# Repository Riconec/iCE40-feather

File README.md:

# iCE40-feather

## An iCE40UP5K FPGA in a Feather compatible form factor

* iCE40UP5k FPGA in a QFN-48 package
    * 5280 Logic Cells
* 20 IO broken out to Feather, 4 additional IO on bottom of board
* FT2232 provides programming and UART interface over a Micro USB connector
* 32 MBit SPI Flash
* Onboard RGB LED, user LED, TX/RX LEDs

### Additional FeatherWings  
* 6x6 LED Matrix + 4 Buttons + RGB LED
* DIP Switch + 7 Segment Display
* Feather to Dual PMOD breakout 

### Software
* Compatible with the open source [IceStorm](http://www.clifford.at/icestorm/#install) toolchain
* Thanks to [Piotr Esden-Tempski](https://twitter.com/esden) and his [iCEBreaker examples](https://github.com/icebreaker-fpga/icebreaker-examples) as a starting point for the firmware development.

### Additional Images

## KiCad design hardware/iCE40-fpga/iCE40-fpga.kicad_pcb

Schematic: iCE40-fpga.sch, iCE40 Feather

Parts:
C1, C2, C4, C10, C18: 10u; C_0603_1608Metric
C3, C7, C8, C11, C16, C19, C21, C22, C24: 100n; C_0603_1608Metric
C5, C6: 1u; C_0603_1608Metric
D1: ORG; LED_0603_1608Metric
D2: MBR120; D_SOD-123F
D3, D8: GRN; LED_0603_1608Metric
D4: CDBU0520; D_SOD-523
D5: BLU; LED_0603_1608Metric
D6: LED_RGBA; LED_0606
D7: RED; LED_0603_1608Metric
F1: 500mA; Fuse_0805_2012Metric
FB1: 600R; Ferrite_Bead_0603
J1: USB_B_Micro; USB_Micro_Aliexpress
J2: JST_PH; JST_PH_S2B-PH-SM4-TB_1x02-1MP_P2.00mm_Horizontal
J3: Feather; featherwing
Q1: DMP2045U; SOT-23
R1, R4: 100K; R_0603_1608Metric
R3, R5: 10K; R_0603_1608Metric
R6: 100R; R_0603_1608Metric
RN1: 10K; R_Array_Convex_4x0402
RN3: 330R; R_Array_Convex_4x0402
RN4, RN5: 2K2; R_Array_Convex_4x0402
TP1: IO_22; TestPoint_Pad_D1.5mm
TP2: IO_20; TestPoint_Pad_D1.5mm
TP3: IO_23; TestPoint_Pad_D1.5mm
TP4: IO_21; TestPoint_Pad_D1.5mm
U1: MCP73831-2-OT; SOT-23-5
U2: W25Q32JVZP; WSON-8-1EP_6x5mm_P1.27mm_EP3.4x4.3mm
U3: AP2112K-3.3; SOT-23-5
U4: ICE40UP5K-SG48ITR; QFN-48-1EP_7x7mm_P0.5mm_EP5.6x5.6mm_ThermalVias
U5: NCV8114ASN120T1G; TSOT-23-5
X1: DSC6101CI1A; CDFN_3.2x2.5mm_XO; MPN DSC6101CI1A-012.0000T

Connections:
+1V2: C6.1, C10.1, C16.1, C18.1, C19.1, C22.1, R6.2, U4.5 (VCC), U4.30 (VCC), U5.5 (OUT)
+5V: D1.2 (A), D2.2 (A), FB1.2, J3.26 (VBUS), Q1.1 (G), R1.1, U1.4 (VDD)
+BATT: C2.1, J2.1, J3.28 (VBAT), Q1.3 (D), U1.3 (VBAT)
/FLASH_MISO|IO1: U2.2 (DO(IO1)), U4.17 (IOB_33b_SPI_SI); also elsewhere on the board
/FLASH_MOSI|IO0: U2.5 (DI(IO0)), U4.14 (IOB_32a_SPI_SO); also elsewhere on the board
/FLASH_SCK: RN1.1 (R1.1), U2.6 (CLK), U4.15 (IOB_34a_SPI_SCK); also elsewhere on the board
/FLASH_SS: RN1.4 (R4.1), U2.1 (~CS), U4.16 (IOB_35b_SPI_SS); also elsewhere on the board
/FLASH_nHOLD|IO3: RN1.3 (R3.1), U2.7 (IO3)
/FLASH_nWP|IO2: RN1.2 (R2.1), U2.3 (IO2)
/ICE_CDONE: D5.2 (A), RN4.2, U4.7 (CDONE); also elsewhere on the board
/ICE_CLK: U4.35 (IOT_46b_G0), X1.3 (OUT); also elsewhere on the board
/IO_0: J3.5 (IO0), U4.25 (IOT_36b)
/IO_1: J3.6 (IO1), U4.26 (IOT_39a)
/IO_2: J3.7 (IO2), U4.27 (IOT_38b)
/IO_3: J3.8 (IO3), U4.28 (IOT_41a)
/IO_4: J3.9 (IO4), U4.36 (IOT_48b)
/IO_5: J3.10 (IO5), U4.31 (IOT_42b)
/IO_6: J3.11 (IO6|SCK), U4.32 (IOT_43a)
/IO_7: J3.12 (IO7|MOSI), U4.37 (IOT_45a_G1)
/IO_8: J3.13 (IO8|MISO), U4.38 (IOT_50b)
/IO_9: J3.14 (IO9|RX), U4.43 (IOT_49a)
/IO_10: J3.15 (IO10|TX), U4.44 (IOB_3b_G6)
/IO_11: J3.17 (IO11|SDA), U4.48 (IOB_4a)
/IO_12: J3.18 (IO12|SCL), U4.2 (IOB_6a)
/IO_13: J3.19 (IO13), U4.3 (IOB_9b)
/IO_14: J3.20 (IO14), U4.4 (IOB_8a)
/IO_15: J3.21 (IO15), U4.6 (IOB_13b)
/IO_16: J3.22 (IO16), U4.9 (IOB_16a)
/IO_17: J3.23 (IO17), U4.10 (IOB_18a)
/IO_18: J3.24 (IO18), U4.11 (IOB_20a)
/IO_19: J3.25 (IO19), U4.12 (IOB_22b)
/LDO_EN: J3.27 (EN), R4.2, U3.3 (EN)
/UART_RX: RN4.6, U4.23 (IOT_37a); also elsewhere on the board
/UART_TX: RN4.5, U4.21 (IOB_23b); also elsewhere on the board
/USB_N: J1.2 (D-); also elsewhere on the board
/USB_P: J1.3 (D+); also elsewhere on the board
/nICE_CRESET: J3.1 (nRST), R5.2, U4.8 (~CRESET); also elsewhere on the board
/nLED: RN5.4, U4.47 (IOB_2a)
/nLED_BLU: RN3.1 (R1.1), U4.39 (RGB0)
/nLED_GRN: RN3.2 (R2.1), U4.40 (RGB1)
/nLED_RED: RN3.4 (R4.1), U4.41 (RGB2)
unnamed: C1.1, C5.1, D2.1 (K), Q1.2 (S), R4.1, U3.1 (VIN), U5.1 (IN), U5.3 (EN)
unnamed: D1.1 (K), RN5.8
unnamed: D4.1 (K), U4.24 (VPP_2V5)
unnamed: D6.1 (RK), RN3.5 (R4.2)
unnamed: D6.2 (GK), RN3.7 (R2.2)
unnamed: D6.3 (BK), RN3.8 (R1.2)
unnamed: D7.1 (K), RN5.5
unnamed: F1.1, FB1.1
unnamed: F1.2, J1.1 (VBUS)
unnamed: R3.1, U1.5 (PROG)
unnamed: R6.1, U4.29 (VCCPLL)
unnamed: RN5.1, U1.1 (STAT)
unnamed: TP1.1, U4.42 (IOT_51a)
unnamed: TP2.1, U4.46 (IOB_0a)
unnamed: TP3.1, U4.45 (IOB_5b)
unnamed: TP4.1, U4.13 (IOB_24a)

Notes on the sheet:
Power Regulation
FPGA Power
RGB LED
SPI Flash
USB / FTDI Programmer / UART
Oscillator
iCE40UP5K FPGA IO
User LED
Feather Footprint
LIPO Charging
LIPO JST Connector
UART LEDs

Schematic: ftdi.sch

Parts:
C26, C30, C31, C32, C33, C34, C35, C36: 100n; C_0603_1608Metric
C28: 4u7; C_0603_1608Metric
FB2, FB3: 600R; BEADC1608X95N
R13: 2K2; R_0603_1608Metric
R14: 10K; R_0603_1608Metric
R15: 12K; R_0603_1608Metric
RN2: 10K; R_Array_Convex_4x0402
U7: 93C46B; SOT-23-6
U8: FT2232H; QFN-64-1EP_9x9mm_P0.5mm_EP4.7x4.7mm_ThermalVias

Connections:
+1V8: C28.1, C30.1, U7.12, U7.37, U7.49, U7.64
/FLASH_MISO|IO1: U7.18; also elsewhere on the board
/FLASH_MOSI|IO0: U7.17; also elsewhere on the board
/FLASH_SCK: U7.16; also elsewhere on the board
/FLASH_SS: U7.21; also elsewhere on the board
/FTDI Programmer / UART/FT_EECLK: RN2.3 (R3.1), U7.62; also elsewhere on the board
/FTDI Programmer / UART/FT_EECS: RN2.2 (R2.1), U7.63; also elsewhere on the board
/FTDI Programmer / UART/FT_EEDATA: R13.1, RN2.4 (R4.1), U7.61; also elsewhere on the board
/ICE_CDONE: U7.23; also elsewhere on the board
/ICE_CLK: U7.2; also elsewhere on the board
/UART_RX: U7.38; also elsewhere on the board
/UART_TX: U7.39; also elsewhere on the board
/USB_N: U7.7; also elsewhere on the board
/USB_P: U7.8; also elsewhere on the board
/nICE_CRESET: U7.24; also elsewhere on the board
unnamed: C31.1, FB2.1, U7.9
unnamed: C32.1, FB3.1, U7.4
unnamed 60: R13.2; also elsewhere on the board
unnamed: R14.1, U7.14
unnamed: R15.1, U7.6

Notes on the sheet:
FTDI Programmer / UART

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
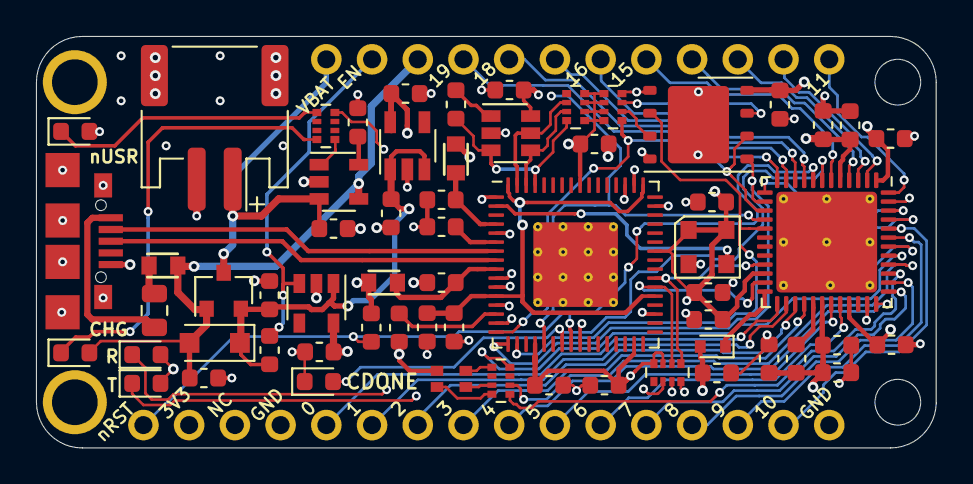
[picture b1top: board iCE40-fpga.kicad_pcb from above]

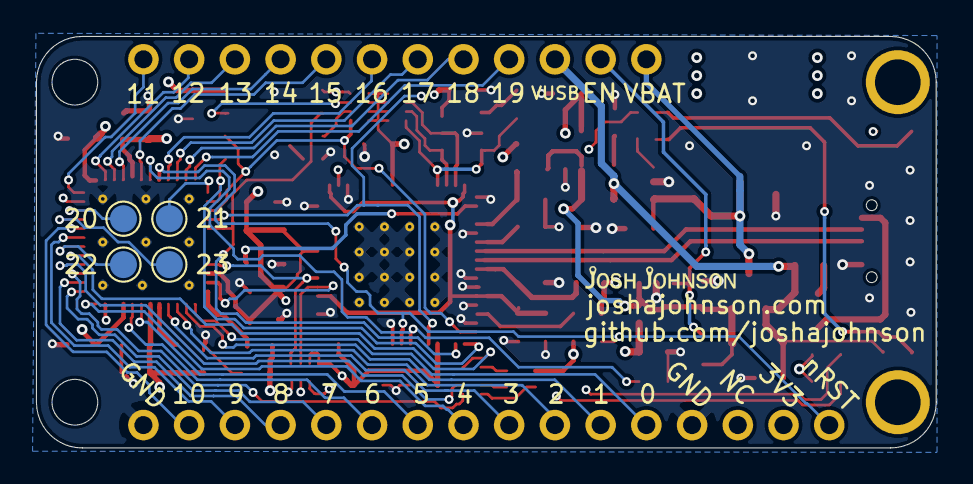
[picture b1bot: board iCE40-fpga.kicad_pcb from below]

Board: 4 copper layers, 50.0 x 22.9 mm, 66 parts (4 on the bottom side), 70 nets.

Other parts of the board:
U6: 93C46B; SOT-23-6

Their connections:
/FTDI Programmer / UART/FT_EECLK: U6.4; also elsewhere on the board
/FTDI Programmer / UART/FT_EECS: U6.5; also elsewhere on the board
/FTDI Programmer / UART/FT_EEDATA: U6.3; also elsewhere on the board
unnamed 60: U6.1; also elsewhere on the board

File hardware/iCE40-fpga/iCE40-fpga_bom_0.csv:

Component,Description,Part,References,Value,Footprint,Quantity Per PCB,Datasheet,MPN
1,Unpolarized capacitor,C,C3 C7 C8 C11 C16 C19 C21 C22 C24 C26 C30 C31 C32 C33 C34 C35 C36,100n,C_0603_1608Metric,17,~,
2,Unpolarized capacitor,C,C1 C2 C4 C10 C18,10u,C_0603_1608Metric,5,~,
3,Unpolarized capacitor,C,C5 C6,1u,C_0603_1608Metric,2,~,
4,Unpolarized capacitor,C,C28,4u7,C_0603_1608Metric,1,~,
5,Light emitting diode,LED,D5,BLU,LED_0603_1608Metric,1,~,
6,Diode,D,D4,CDBU0520,D_SOD-523,1,~,
7,Light emitting diode,LED,D7,LED,LED_0603_1608Metric,1,~,
8,"RGB LED, anode/red/green/blue",LED_RGBA,D6,LTST-C19HE1WT,0606LED,1,~,
9,Schottky diode,D_Schottky,D2,MBR120,D_SOD-123F,1,~,
10,Light emitting diode,LED,D1,ORG,LED_0603_1608Metric,1,~,
11,"Resettable fuse, polymeric positive temperature coefficient",Polyfuse,F1,500mA,Fuse_0805_2012Metric,1,~,
12,Ferrite bead,Ferrite_Bead_PWR,FB1 FB2 FB3,600R ,BEADC1608X95N,3,~,
13,,Feather,J3,Feather,PCB_FeatherWing,1,,
14,"Generic connector, single row, 01x02, script generated (kicad-library-utils/schlib/autogen/connector/)",Conn_01x02_Male,J2,JST_PH,JST_PH_S2B-PH-SM4-TB_1x02-1MP_P2.00mm_Horizontal,1,~,
15,USB Micro Type B connector,USB_B_Micro,J1,USB_B_Micro,MicroUSB_Aliexpress,1,~,
16,"P-MOSFET transistor, gate/source/drain",Q_PMOS_GSD,Q1,DMP2045U,SOT-23,1,~,
17,Resistor,R,R1 R4,100K,R_0603_1608Metric,2,~,
18,Resistor,R,R6,100R,R_0603_1608Metric,1,~,
19,Resistor,R,R3 R5 R14,10K,R_0603_1608Metric,3,~,
20,Resistor,R,R15,12K,R_0603_1608Metric,1,~,
21,Resistor,R,R8,1K,R_0603_1608Metric,1,~,
22,Resistor,R,R2 R7 R13,2K2,R_0603_1608Metric,3,~,
23,"4 resistor network, parallel topology, DIP package",R_Pack04,RN1 RN2,10K,R_Array_Convex_4x0402,2,~,
24,"4 resistor network, parallel topology, DIP package",R_Pack04,RN3,1K,R_Array_Convex_4x0402,1,~,
25,"Serial EEPROM, 93 Series, 5.0V, DIP-8/SOIC-8",93C46B,U7,93C46B,SOT-23-6,1,http://ww1.microchip.com/downloads/en/DeviceDoc/20001749K.pdf,
26,"600mA low dropout linear regulator, with enable pin, 2.5V-6V input voltage range, 1.2V fixed positive output, SOT-23-5 package",AP2112K-1.2,U5,AP2112K-1.2,SOT-23-5,1,https://www.diodes.com/assets/Datasheets/AP2112.pdf,
27,"600mA low dropout linear regulator, with enable pin, 3.8V-6V input voltage range, 3.3V fixed positive output, SOT-23-5 package",AP2112K-3.3,U3,AP2112K-3.3,SOT-23-5,1,https://www.diodes.com/assets/Datasheets/AP2112.pdf,
28,"FT2232Hx, Hi Speed Double Channel USB UART/FIFO, LQFP/QFN-64",FT2232H,U8,FT2232H,QFN-64-1EP_9x9mm_P0.5mm_EP4.7x4.7mm_ThermalVias,1,http://www.ftdichip.com/Products/ICs/FT2232H.html,
29,"iCE40 UltraPlus FPGA, 5280 LUTs, 1.2V, 48-pin QFN",ICE40UP5K-SG48ITR,U6,ICE40UP5K-SG48ITR,QFN-48-1EP_7x7mm_P0.5mm_EP5.3x5.3mm_ThermalVias,1,http://www.latticesemi.com/Products/FPGAandCPLD/iCE40Ultra,
30,"Single cell, Li-Ion/Li-Po charge management controller, 4.20V, Tri-State Status Output, in SOT23-5 package",MCP73831-2-OT,U1,MCP73831-2-OT,SOT-23-5,1,http://ww1.microchip.com/downloads/en/DeviceDoc/20001984g.pdf,
31,"32Mb Serial Flash Memory, Standard/Dual/Quad SPI, DFN-8",W25Q32JVZP,U2,W25Q32JVZP,WSON-8-1EP_6x5mm_P1.27mm_EP3.4x4.3mm,1,http://www.winbond.com/resource-files/w25q32jv%20revg%200327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,
32,MEMS OSC 12MHz,DSC6101CI1A,X1,DSC6101CI1A,CDFN_3.2x2.5mm_XO,1,,DSC6101CI1A-012.0000T





Component Groups:,32
Component Count:,61
Fitted Components:,61
Number of PCBs:,1
Total components:,61
Schematic Version:,0
Schematic Date:,2019-06-24
BoM Date:,25/06/2019 12:15:57
Schematic Source:,C:\Users\Josh Johnson\Dropbox\Projects\iCE40-fpga\hardware\iCE40-fpga\iCE40-fpga.sch
KiCad Version:,Eeschema (5.1.2)-1

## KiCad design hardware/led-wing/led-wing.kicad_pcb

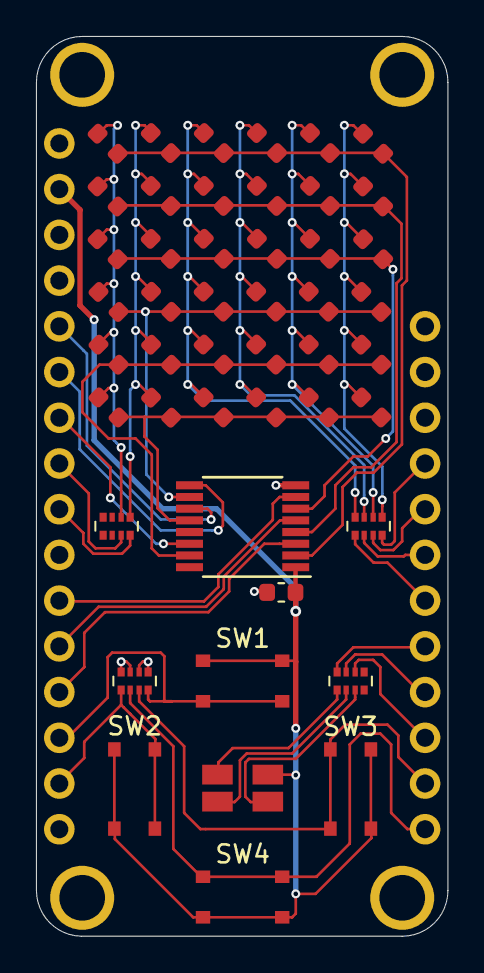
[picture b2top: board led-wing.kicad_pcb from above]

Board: 2 copper layers, 22.9 x 50.0 mm, 48 parts (0 on the bottom side), 36 nets.

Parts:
C1: 100n; C_0603_1608Metric
D1: LED_RGBA; LED_ARGB_PLCC4_1210
D2, D3, D4, D5, D6, D7, D8, D9, D10, D11, D12, D13, D14, D15, D16, D17, D18, D19, D20, D21, D22, D23, D24, D25, D26, D27, D28, D29, D30, D31, D32, D33, D34, D35, D36, D37: LED; LED_0603_1608Metric_45_noSilk
J1: Feather; featherwing
RN1: 10K; R_Array_Convex_4x0402
RN2, RN3, RN4: 330R; R_Array_Convex_4x0402
SW1, SW2, SW3, SW4: SW_Push; BT_PTS815
U1: CD74HC4050; TSSOP-16_4.4x5mm_P0.65mm

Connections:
+3V3: C1.1, D1.4, J1.2, SW1.1, SW2.1, SW3.1, SW4.1, U1.1
/BT1: J1.14, RN1.8, SW1.2
/BT2: J1.15, RN1.5, SW2.2
/BT3: J1.18, RN1.7, SW3.2
/BT4: J1.17, RN1.6, SW4.2
/C1: D32.1, D33.1, D34.1, D35.1, D36.1, D37.1, RN2.6
/C2: D26.1, D27.1, D28.1, D29.1, D30.1, D31.1, RN2.5
/C3: D20.1, D21.1, D22.1, D23.1, D24.1, D25.1, RN4.8
/C4: D14.1, D15.1, D16.1, D17.1, D18.1, D19.1, RN4.7
/C5: D8.1, D9.1, D10.1, D11.1, D12.1, D13.1, RN4.6
/C6: D2.1, D3.1, D4.1, D5.1, D6.1, D7.1, RN4.5
/COL_1: J1.8, RN2.3
/COL_2: J1.9, RN2.4
/COL_3: J1.22, RN4.1
/COL_4: J1.23, RN4.2
/COL_5: J1.24, RN4.3
/COL_6: J1.25, RN4.4
/R1: D2.2, D8.2, D14.2, D20.2, D26.2, D32.2, U1.2
/R2: D3.2, D9.2, D15.2, D21.2, D27.2, D33.2, U1.4
/R3: D4.2, D10.2, D16.2, D22.2, D28.2, D34.2, U1.6
/R4: D5.2, D11.2, D17.2, D23.2, D29.2, D35.2, U1.10
/R5: D6.2, D12.2, D18.2, D24.2, D30.2, D36.2, U1.15
/R6: D7.2, D13.2, D19.2, D25.2, D31.2, D37.2, U1.12
/ROW_1: J1.13, U1.3
/ROW_2: J1.12, U1.5
/ROW_3: J1.11, U1.7
/ROW_4: J1.6, U1.9
/ROW_5: J1.7, U1.14
/ROW_6: J1.5, U1.11
/nLED_B: J1.19, RN3.2
/nLED_G: J1.20, RN3.3
/nLED_R: J1.21, RN3.4
GND: C1.2, J1.4, J1.16, RN1.1, RN1.2, RN1.3, RN1.4, U1.8
unnamed: D1.1, RN3.5
unnamed: D1.2, RN3.6
unnamed: D1.3, RN3.7

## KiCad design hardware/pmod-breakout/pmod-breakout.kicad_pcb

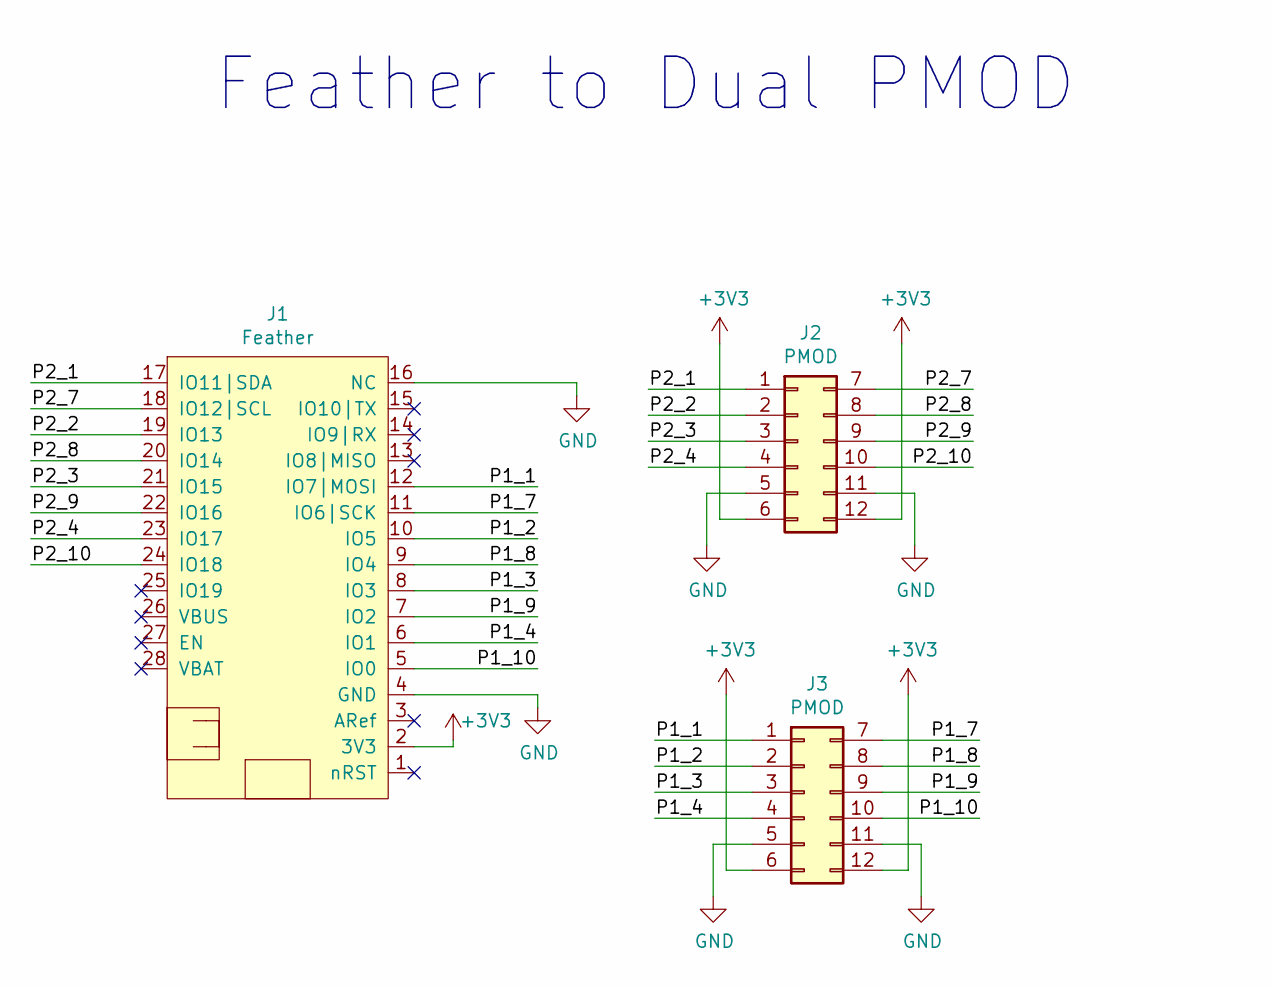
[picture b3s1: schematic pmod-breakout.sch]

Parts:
J1: Feather; featherwing
J2, J3: PMOD; PMOD_HOST

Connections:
+3V3: J1.2 (3V3), J2.6, J2.12, J3.6, J3.12
/P1_1: J1.12 (IO7|MOSI), J3.1
/P1_2: J1.10 (IO5), J3.2
/P1_3: J1.8 (IO3), J3.3
/P1_4: J1.6 (IO1), J3.4
/P1_7: J1.11 (IO6|SCK), J3.7
/P1_8: J1.9 (IO4), J3.8
/P1_9: J1.7 (IO2), J3.9
/P1_10: J1.5 (IO0), J3.10
/P2_1: J1.17 (IO11|SDA), J2.1
/P2_2: J1.19 (IO13), J2.2
/P2_3: J1.21 (IO15), J2.3
/P2_4: J1.23 (IO17), J2.4
/P2_7: J1.18 (IO12|SCL), J2.7
/P2_8: J1.20 (IO14), J2.8
/P2_9: J1.22 (IO16), J2.9
/P2_10: J1.24 (IO18), J2.10
GND: J1.4 (GND), J1.16 (NC), J2.5, J2.11, J3.5, J3.11

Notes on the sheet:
Feather to Dual PMOD

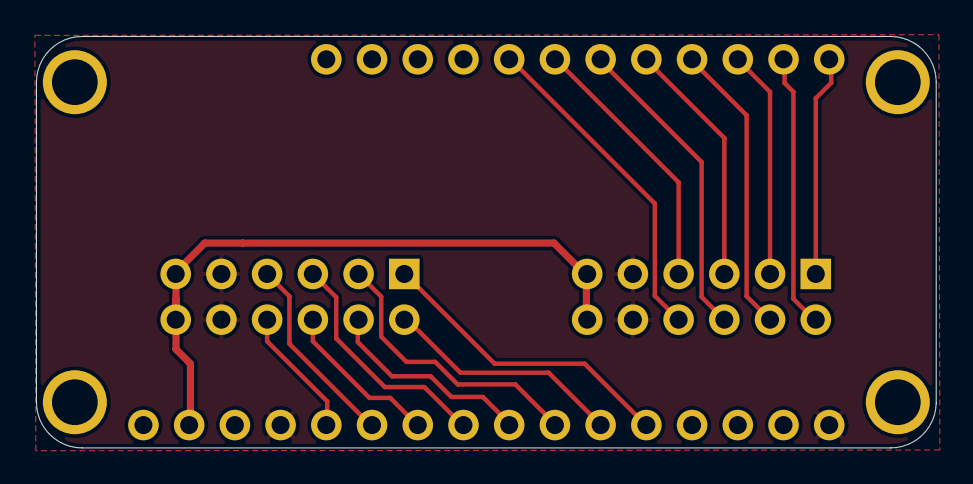
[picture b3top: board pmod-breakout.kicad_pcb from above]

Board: 2 copper layers, 50.0 x 22.9 mm, 3 parts (0 on the bottom side), 18 nets.

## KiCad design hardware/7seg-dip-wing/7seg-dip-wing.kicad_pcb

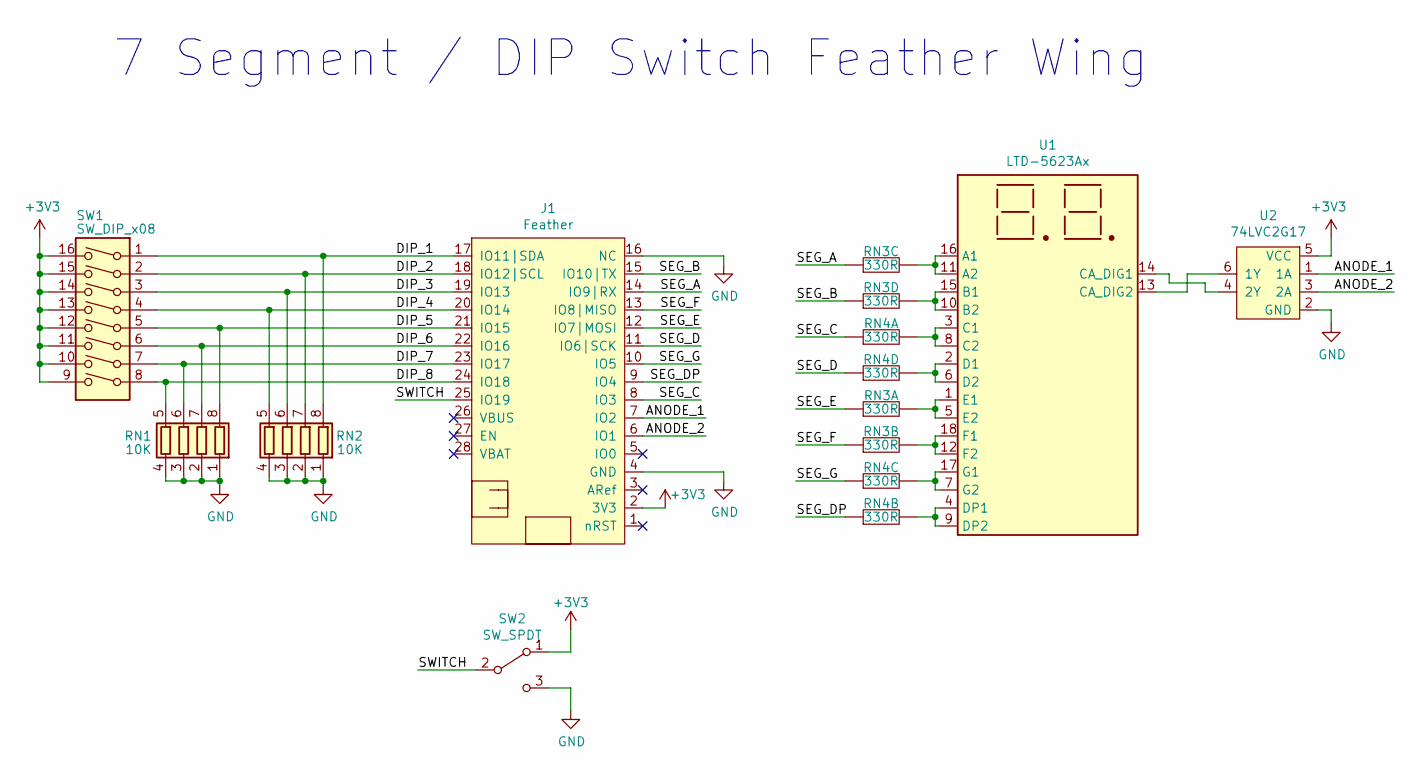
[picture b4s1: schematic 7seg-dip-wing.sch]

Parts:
J1: Feather; featherwing
RN1, RN2: 10K; R_Array_Convex_4x0402
RN3, RN4: 330R; R_Array_Convex_4x0402
SW1: SW_DIP_x08; SW_DIP_SPSTx08_Slide_9.78x22.5mm_W7.62mm_P2.54mm
SW2: SW_SPDT; SW_SPDT_PCM12
U1: LTD-5623Ax; DA56-11SEKWA
U2: 74LVC2G17; SOT-363_SC-70-6

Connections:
+3V3: J1.2 (3V3), SW1.9, SW1.10, SW1.11, SW1.12, SW1.13, SW1.14, SW1.15, SW1.16, SW2.1 (A), U2.5 (VCC)
/ANODE_1: J1.7 (IO2), U2.1 (1A)
/ANODE_2: J1.6 (IO1), U2.3 (2A)
/DIP_1: J1.17 (IO11|SDA), RN2.8 (R1.2), SW1.1
/DIP_2: J1.18 (IO12|SCL), RN2.7 (R2.2), SW1.2
/DIP_3: J1.19 (IO13), RN2.6 (R3.2), SW1.3
/DIP_4: J1.20 (IO14), RN2.5 (R4.2), SW1.4
/DIP_5: J1.21 (IO15), RN1.8 (R1.2), SW1.5
/DIP_6: J1.22 (IO16), RN1.7 (R2.2), SW1.6
/DIP_7: J1.23 (IO17), RN1.6 (R3.2), SW1.7
/DIP_8: J1.24 (IO18), RN1.5 (R4.2), SW1.8
/SEG_A: J1.14 (IO9|RX), RN3.2
/SEG_B: J1.15 (IO10|TX), RN3.1
/SEG_C: J1.8 (IO3), RN4.4
/SEG_D: J1.11 (IO6|SCK), RN4.1
/SEG_DP: J1.9 (IO4), RN4.3
/SEG_E: J1.12 (IO7|MOSI), RN3.4
/SEG_F: J1.13 (IO8|MISO), RN3.3
/SEG_G: J1.10 (IO5), RN4.2
/SWITCH: J1.25 (IO19), SW2.2 (B)
GND: J1.4 (GND), J1.16 (NC), RN1.1 (R1.1), RN1.2 (R2.1), RN1.3 (R3.1), RN1.4 (R4.1), RN2.1 (R1.1), RN2.2 (R2.1), RN2.3 (R3.1), RN2.4 (R4.1), SW2.3 (C), U2.2 (GND)
unnamed: RN3.5, U1.1 (E1), U1.5 (E2)
unnamed: RN3.6, U1.12 (F2), U1.18 (F1)
unnamed: RN3.7, U1.11 (A2), U1.16 (A1)
unnamed: RN3.8, U1.10 (B2), U1.15 (B1)
unnamed: RN4.5, U1.3 (C1), U1.8 (C2)
unnamed: RN4.6, U1.4 (DP1), U1.9 (DP2)
unnamed: RN4.7, U1.7 (G2), U1.17 (G1)
unnamed: RN4.8, U1.2 (D1), U1.6 (D2)
unnamed: U1.13 (CA_DIG2), U2.6 (1Y)
unnamed: U1.14 (CA_DIG1), U2.4 (2Y)

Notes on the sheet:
7 Segment / DIP Switch Feather Wing

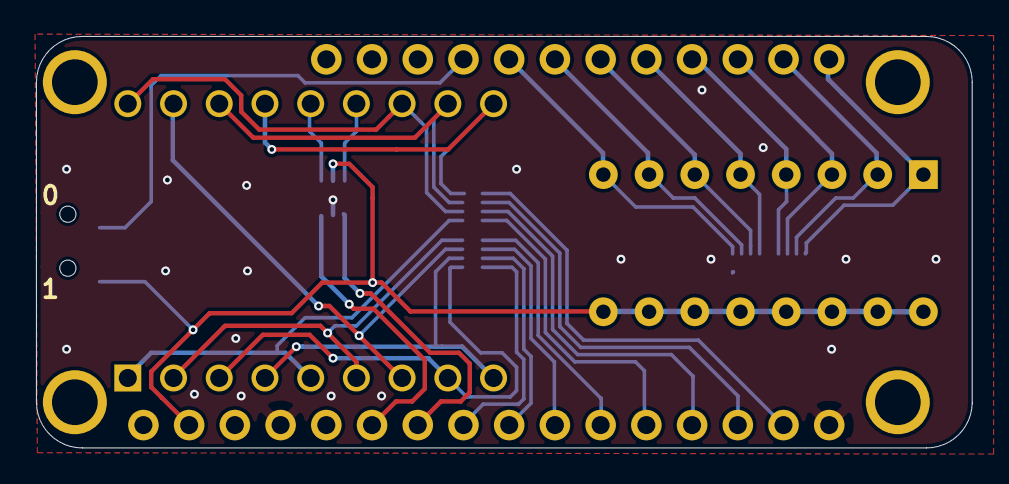
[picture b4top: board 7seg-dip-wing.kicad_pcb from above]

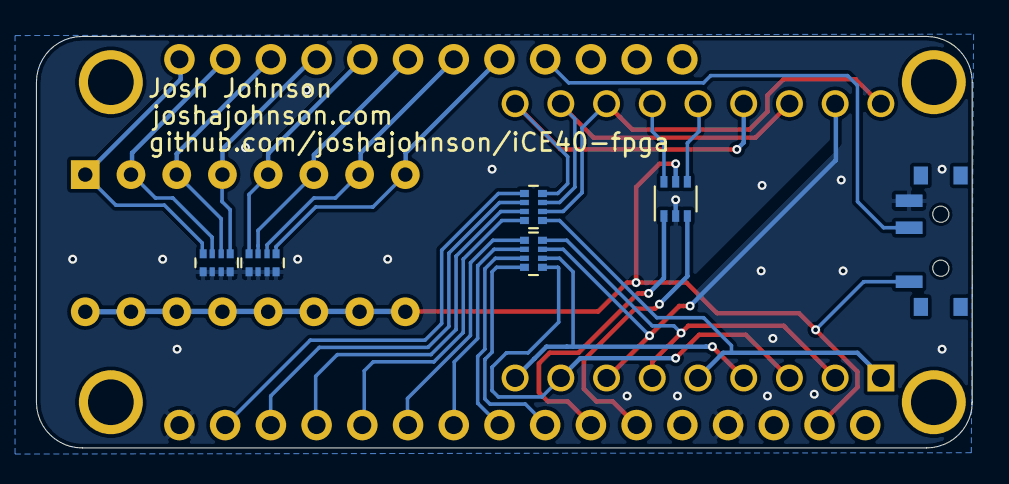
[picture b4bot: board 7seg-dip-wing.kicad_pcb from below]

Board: 2 copper layers, 52.0 x 22.9 mm, 9 parts (6 on the bottom side), 31 nets.

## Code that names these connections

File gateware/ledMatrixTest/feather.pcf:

# 12 MHz clock
set_io -nowarn clk        	35

# User LED
set_io -nowarn nLED 		47

# RGB LED
set_io -nowarn nLED_RED  	41
set_io -nowarn nLED_GRN  	40
set_io -nowarn nLED_BLU  	39

# LED Matrix RGB LED
set_io -nowarn nLED_RED_fw  6
set_io -nowarn nLED_GRN_fw  4
set_io -nowarn nLED_BLU_fw	3

# LED Matrix Pins
set_io -nowarn row[0]		38
set_io -nowarn row[1]		37
set_io -nowarn row[2]		32
set_io -nowarn row[3]		26
set_io -nowarn row[4]		27
set_io -nowarn row[5]		25

set_io -nowarn col[0]		28
set_io -nowarn col[1]		36
set_io -nowarn col[2]		9
set_io -nowarn col[3]		10
set_io -nowarn col[4]		11
set_io -nowarn col[5]		12

set_io -nowarn btn[0]		43
set_io -nowarn btn[1]		44
set_io -nowarn btn[2]		2
set_io -nowarn btn[3]		48

# GPIO
set_io -nowarn IO_0 		25
set_io -nowarn IO_1 		26
set_io -nowarn IO_2 		27
set_io -nowarn IO_3 		28
set_io -nowarn IO_4 		36
set_io -nowarn IO_5 		31
set_io -nowarn IO_6 		32
set_io -nowarn IO_7 		37
set_io -nowarn IO_8 		38
set_io -nowarn IO_9 		43
set_io -nowarn IO_10 		44
set_io -nowarn IO_11 		48
set_io -nowarn IO_12 		2
set_io -nowarn IO_13 		3
set_io -nowarn IO_14 		4
set_io -nowarn IO_15 		6
set_io -nowarn IO_16 		9
set_io -nowarn IO_17		10
set_io -nowarn IO_18		11
set_io -nowarn IO_19 		12
set_io -nowarn IO_20 		46
set_io -nowarn IO_21 		13
set_io -nowarn IO_22 		42
set_io -nowarn IO_23 		45

# UART
set_io -nowarn UART_RX 		23
set_io -nowarn UART_TX 		21

# SPI Flash
set_io -nowarn FLASH_SCK  	15
set_io -nowarn FLASH_SS  	16
set_io -nowarn FLASH_MOSI  	14
set_io -nowarn FLASH_MISO  	17

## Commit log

2019-06-24 prelim schematic done + all footprints associated
2019-06-24 fixed footprints + added extra feather headers
2019-06-24 all nets routed
2019-06-25 cleaned up routing
2019-06-26 added tx, rx leds, 7 segment and pmod wings
2019-06-26 updated board + pmod
2019-06-26 changes to make everything work with new library setup
2019-06-26 fixing things which broke resulting from library change
2019-07-06 added multiplexing featherwing
2019-07-07 broke out 4 pins to TP on bottom copper
2019-07-25 Added gateware
2019-07-25 generated gerbers, changed pin labelling to match constraints file
2019-07-25 fixed LED footprint + power supply change to support battery
2019-07-26 started test file
2019-07-26 makefiles working with simulation
2019-07-26 keep uart leds off while not in use
2019-07-28 generating BOM and costing things
2019-07-29 added pdf schematics
2019-07-29 7 seg decoding works
2019-07-29 matrix now working
2019-07-29 changed TX RX led direction
2019-08-01 update test script
2019-08-05 updated feather footprint
2019-08-05 updated josh's details
2019-08-07 cleaned up 7 segment code
2019-08-08 moved battery connector and generated new gerbers for FPGA
2019-08-09 cropped images
2019-08-09 nextpnr now runs in quiet mode
2019-08-09 removed incomplete BOM
2019-08-10 seven segment handles display overflow better
2019-08-10 added nLED button control to led matrix wing
2019-08-11 words are hard
2019-08-13 changing blink for WTFpga
2019-08-13 blink for WTFpga working
2019-08-14 updated BOM
2019-08-14 updated seven seg code for common anode
2019-08-19 updated seven seg schematic
2019-08-31 added (untested) debounce gateware
2019-08-31 added short readme to each module
2019-09-06 begun snake
2019-09-06 first test at shitty snake
2019-09-06 can move dot around
2019-09-06 can move dot without hacks
2019-09-09 added new to makefile to init new folder
2019-09-11 Swap RGB blue / red pin assignments
2019-09-26 added pwm and moved gateware files
2019-09-28 clean up matrix code
2019-10-03 more snake progress + ported tnt's rgb_panel over
2019-10-04 dodge the walls is working
2019-10-04 moved snake into dot folder
2019-10-04 more snake progress + significant simulation improvements
2019-10-25 gave up on snake, now dot
2019-10-25 uart display RX working
2019-10-25 Finished demo code
2019-11-25 add gen_gamma_table.c
2020-01-07 add eeprom config to mimic lattice cable
2020-01-14 add blinky example
2020-01-14 trials for bram
